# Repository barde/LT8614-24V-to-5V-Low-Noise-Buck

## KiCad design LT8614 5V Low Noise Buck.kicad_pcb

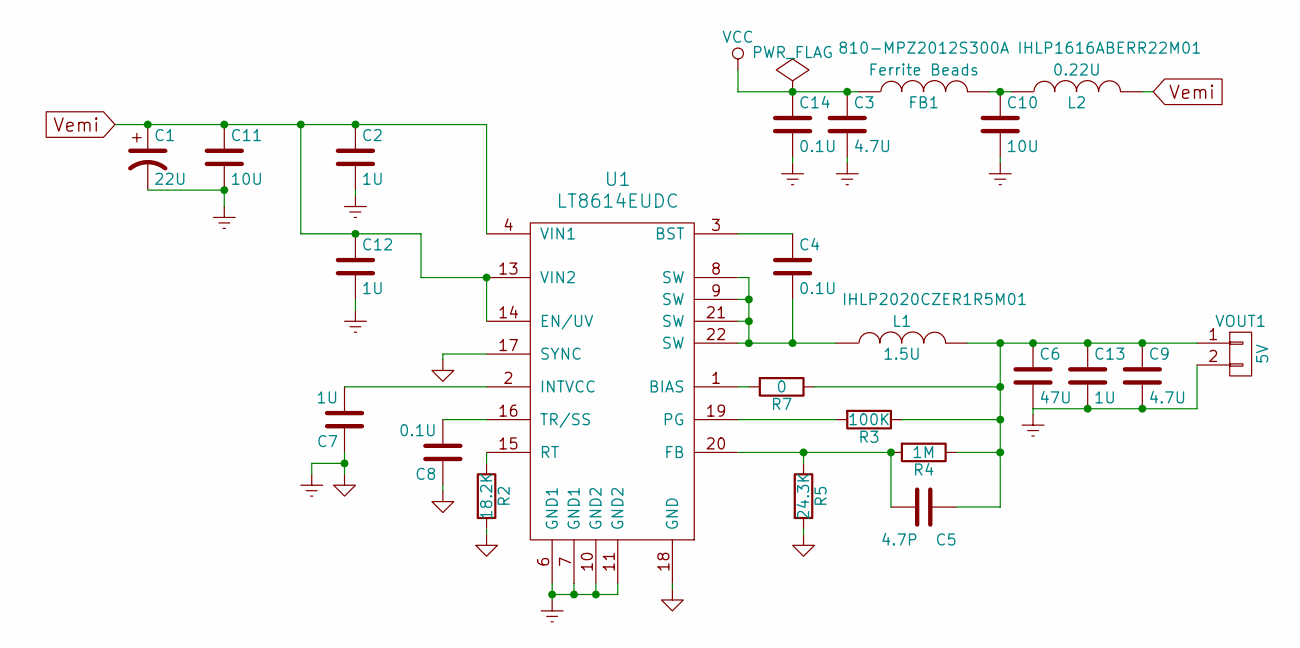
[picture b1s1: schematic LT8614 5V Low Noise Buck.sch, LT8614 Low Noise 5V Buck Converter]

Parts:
C1: 22U; c_elec_6.3x5.8
C2, C7, C12, C13: 1U; C_0603_HandSoldering
C3: 4.7U; C_1206_HandSoldering
C4, C8: 0.1U; C_0603_HandSoldering
C5: 4.7P; C_0603_HandSoldering
C6: 47U; C_1210_HandSoldering
C9: 4.7U; C_0603_HandSoldering
C10: 10U; C_1210_HandSoldering
C11: 10U; C_1206_HandSoldering
C14: 0.1U; C_0402
FB1: Ferrite Beads; C_0805
L1: 1.5U; inductor-smd-2020-50x50
L2: 0.22U; Inductor_Taiyo-Yuden_MD-4040
R2: 18.2K; R_0603_HandSoldering
R3: 100K; R_0603_HandSoldering
R4: 1M; R_0603_HandSoldering
R5: 24.3K; R_0603_HandSoldering
R7: 0; R_0603_HandSoldering
U1: LT8614EUDC; LT8614
VOUT1: 5V; Pin_Header_Straight_1x02

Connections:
GND: C1.2, C2.2, C3.2, C6.2, C7.1, C8.1, C9.2, C10.2, C11.2, C12.2, C13.2, C14.2, R2.2, R5.2, U1.6 (GND1), U1.7 (GND1), U1.10 (GND2), U1.11 (GND2), U1.17 (SYNC), U1.18 (GND), VOUT1.2
unnamed: C4.1, U1.3 (BST)
unnamed: C4.2, L1.1, U1.8 (SW), U1.9 (SW), U1.21 (SW), U1.22 (SW)
unnamed: C5.2, R4.2, R5.1, U1.20 (FB)
unnamed: C7.2, U1.2 (INTVCC)
unnamed: C8.2, U1.16 (TR/SS)
unnamed: C10.1, FB1.2, L2.1
unnamed: C5.1, C6.1, C9.1, C13.1, L1.2, R3.1, R4.1, R7.1, VOUT1.1
unnamed: R2.1, U1.15 (RT)
unnamed: R3.2, U1.19 (PG)
unnamed: R7.2, U1.1 (BIAS)
VCC: C3.1, C14.1, FB1.1
Vemi: C1.1, C2.1, C11.1, C12.1, L2.2, U1.4 (VIN1), U1.13 (VIN2), U1.14 (EN/UV)

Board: 2 copper layers, 24 parts (0 on the bottom side), 13 nets, no tracks yet.

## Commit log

2017-01-03 init
2017-01-08 netlist and first pcb draft
